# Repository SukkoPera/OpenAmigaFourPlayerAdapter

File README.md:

# OpenAmigaFourPlayerAdapter
OpenAmigaFourPlayerAdapter is an Open Hardware adapter that allows connecting two additional joysticks to Amiga Computers, bringing the total to four.

## Summary
Some Amiga Games support more than the two joysticks you can connect directly to all Amiga models. The two extra joysticks are supposed to be connected to the parallel port through an adapter. OpenAmigaFourPlayerAdapter is an Open Hardware implementation of such an adapter, based on [Tomi Engdahl's Multi-joystick extender circuit](https://www.epanorama.net/documents/joystick/amiga_circuits.html), which claims to be the de-facto standard for this. The same circuit was found on other sources, so this should not be too far away from the actual truth.

The adapter slightly improves that design by also providing 5V power to the joystick ports. Finally, its apparently odd shape allows it not to bump into the nearby power/audio cables that will be connected to your Amiga.

Testing was only carried out with DynaBlaster. [Here is a list](https://aminet.net/package/docs/misc/FourPlayerGames_EN) of more games that *should* hopefully work with it. Actually the list includes the same circuit the adapter is based on, so there are good chances this will be the case. Please report any failures.

## Assembly and Usage
Building the adapter is very easy, just note that you need all male connectors, for both the DB-9 and the DB-25 ports.

The adapter needs no configuration. The only option is whether the 5V power pins of the joystick ports should actually be powered or not. The adapter itself is fully passive and consumes no current. Most old-style joysticks do not need power either, but if you are using one with autofire functionalities or maybe [some "complex" adapter](https://github.com/SukkoPera/OpenPSX2AmigaPadAdapter), it probably will. Now, the problem is that parallel ports are only required to supply a current of 10 mA, which is very little and probably not enough for even the simplest controller that needs power.

Luckily, most (if not all) Amiga models actually go beyond that and are able to provide about 100 mA. I really recommend you to check personally what is inside your Amiga: there should be a  current-limiting resistor connected to pin 14 of the parallel port (It should be labeled E501 on the A500): I found out that this is usually 47 ohm 1/2 W (I checked on an A500 rev 8A, an A600 rev 1.5 and an A1200 rev 1D.4). If this is your case as well, then you will be fine, but **please make sure this applies to your Amiga, or you might blow that resistor**! You have been warned, I take no responsibility!

Once you are sure your Amiga can bear the current, just close the jumper placed near the port(s) of interest.

Finally, please note that you are recommended to **only connect/disconnect the adapter and the joysticks while your Amiga is powered off**, in order to avoid any risk of damage.

## Releases
If you want to get this board produced, you are recommended to get [the latest release](https://github.com/SukkoPera/OpenAmigaFourPlayerAdapter/releases) rather than the current git version, as the latter might be under development and is not guaranteed to be working.

Every release is accompanied by its Bill Of Materials (BOM) file and any relevant notes about it, which you are recommended to read carefully.

**I am not providing ready-to-use gerber files**. If all you want is **to get boards made, I would really appreciate if you did so [in a way that supports the project](#support-the-project)**.

### Enclosure
One 3D-printable enclosure is currently available for this board:

- Kindly contribution by Youen Chéné available in [enclosure](./enclosure) folder. It needs 2 screws for assembly.

## License
The OpenAmigaFourPlayerAdapter documentation, including the design itself, is copyright &copy; SukkoPera 2020.

OpenAmigaFourPlayerAdapter is Open Hardware licensed under the [CERN OHL v. 1.2](http://ohwr.org/cernohl).

You may redistribute and modify this documentation under the terms of the CERN OHL v.1.2. This documentation is distributed *as is* and WITHOUT ANY EXPRESS OR IMPLIED WARRANTIES whatsoever with respect to its functionality, operability or use, including, without limitation, any implied warranties OF MERCHANTABILITY, SATISFACTORY QUALITY, FITNESS FOR A PARTICULAR PURPOSE or infringement. We expressly disclaim any liability whatsoever for any direct, indirect, consequential, incidental or special damages, including, without limitation, lost revenues, lost profits, losses resulting from business interruption or loss of data, regardless of the form of action or legal theory under which the liability may be asserted, even if advised of the possibility or likelihood of such damages.

A copy of the full license is included in file [LICENSE.pdf](LICENSE.pdf), please refer to it for applicable conditions. In order to properly deal with its terms, please see file [LICENSE_HOWTO.pdf](LICENSE_HOWTO.pdf).

The contact points for information about manufactured Products (see section 4.2) are listed in file [PRODUCT.md](PRODUCT.md).

Any modifications made by Licensees (see section 3.4.b) shall be recorded in file [CHANGES.md](CHANGES.md).

The Documentation Location of the original project is https://github.com/SukkoPera/OpenAmigaFourPlayerAdapter/.

## Support the Project
If you want to support the project, you can order the boards from PCBWay through this link:

You get my gratitude and cheap, good quality PCBs, professionally-made. I get some credit that will help with this and [other projects](https://www.pcbway.com/project/member/shareproject/?bmbid=41100). You won't even have to worry about the various PCB options, it's all pre-configured for you!

If you still have to register to that site, [you can use this link](https://www.pcbway.com/setinvite.aspx?inviteid=41100) to get some bonus initial credit (and yield me some more).

You can also buy me a coffee if you want:

## Get Help
If you need help or have any questions or suggestions, you can join `#OpenRetroWorks` on FreeNode through your favorite IRC client or [the webchat](https://webchat.freenode.net/), or [the official Telegram group](https://t.me/joinchat/HUHdWBC9J9JnYIrvTYfZmg).

## Thanks
- Graham P. for sending me the design of a similar adapter he was working on.
- Tomi Engdahl for publishing the circuit.

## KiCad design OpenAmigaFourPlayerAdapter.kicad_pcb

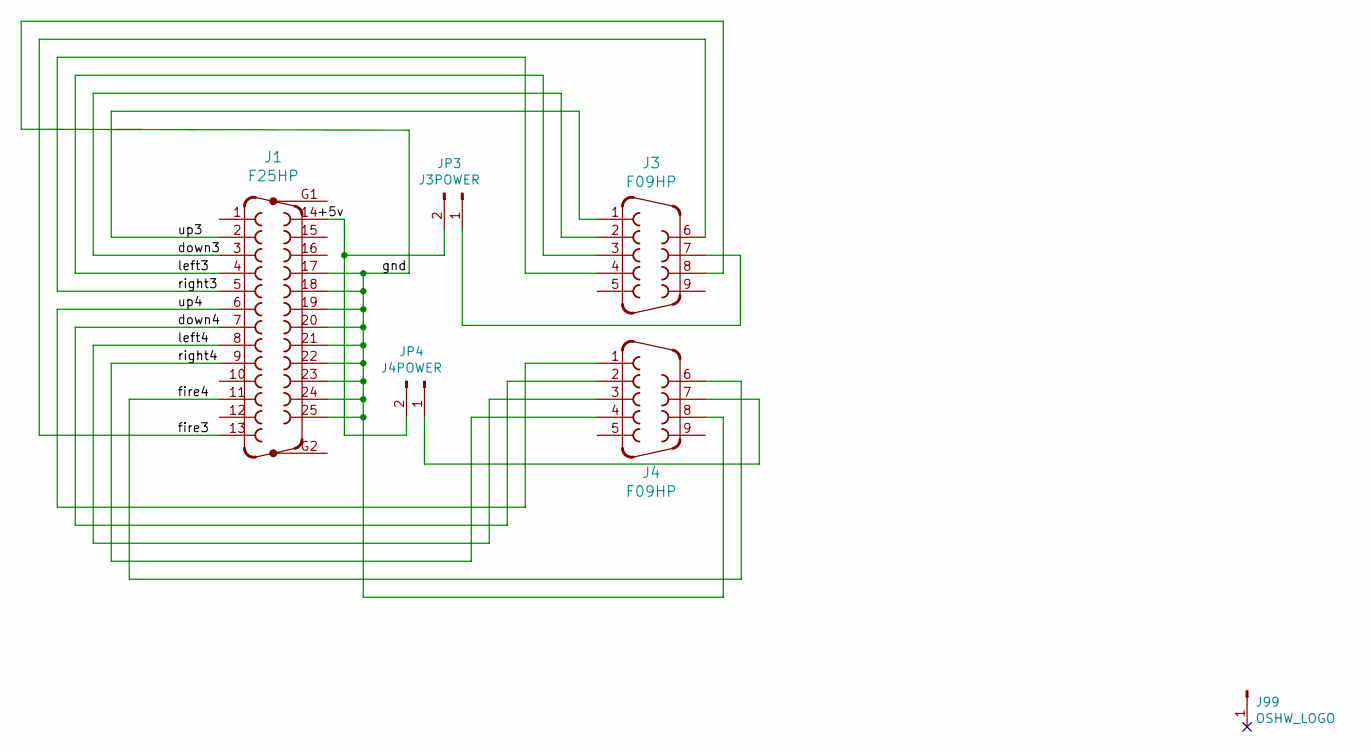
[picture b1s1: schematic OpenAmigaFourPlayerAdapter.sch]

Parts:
J1: F25HP; DSUB-25_Male_EdgeMount_P2.77mm
J3, J4: F09HP; DSUB-9_Male_EdgeMount_P2.77mm
J99: OSHW_LOGO; OSHW-Logo_5.7x6mm_Copper
JP3: J3POWER; PinHeader_1x02_P2.54mm_Vertical
JP4: J4POWER; PinHeader_1x02_P2.54mm_Vertical

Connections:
/+5v: J1.14, JP3.2, JP4.2
/down3: J1.3, J3.2
/down4: J1.7, J4.2
/fire3: J1.13, J3.6
/fire4: J1.11, J4.6
/gnd: J1.17, J1.18, J1.19, J1.20, J1.21, J1.22, J1.23, J1.24, J1.25, J3.8, J4.8
/left3: J1.4, J3.3
/left4: J1.8, J4.3
/right3: J1.5, J3.4
/right4: J1.9, J4.4
/up3: J1.2, J3.1
/up4: J1.6, J4.1
unnamed: J3.7, JP3.1
unnamed: J4.7, JP4.1

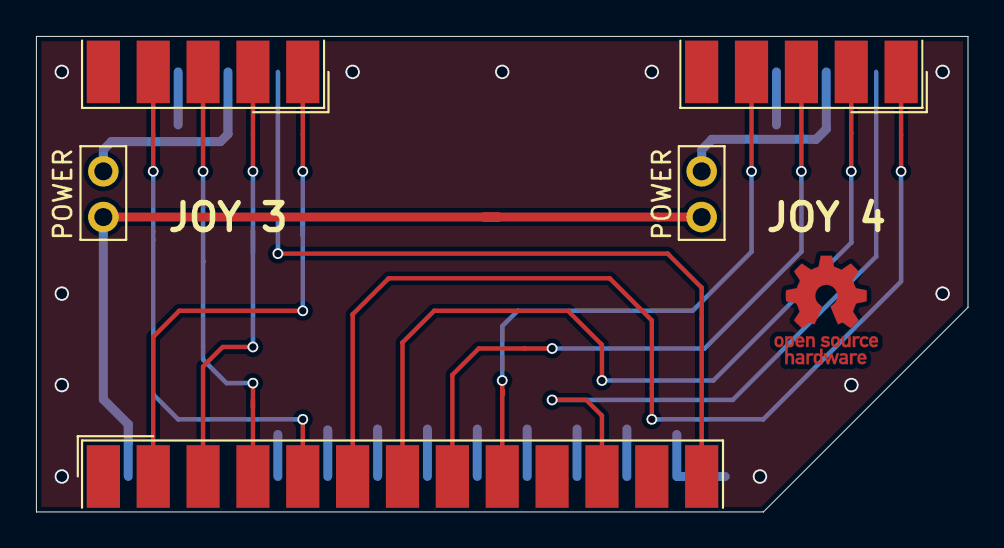
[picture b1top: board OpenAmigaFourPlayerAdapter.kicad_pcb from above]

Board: 2 copper layers, 51.8 x 26.4 mm, 6 parts (0 on the bottom side), 14 nets.

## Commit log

2020-01-02 4 Player Adapter.* -> OpenAmigaFourPlayerAdapter.*
2020-02-11 Add 3D model for DB-9 connector
2020-02-11 Fix minor issue with copper pour
2020-02-11 Make shape symmetrical (but not yet suitable for A600/1200)
2020-02-17 Change shape so that we don't bump in audio connectors on A600/A1200
2020-02-18 Fix board outline
2020-02-18 Make board slightly shorter
2020-02-18 Add renders
2020-02-18 Add license
2020-02-18 Add README.md
2020-02-19 Fix credits
2020-02-22 Improve ground stitching
2020-03-19 Ready for V2
2020-05-24 Add fp-info-cache to .gitignore
2020-05-24 Fix boards link
2020-05-24 Add social image
2023-05-15 feat: add 3D printed enclosure
2023-11-04 feat: new enclosure for m3 screws

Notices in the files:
OpenAmigaFourPlayerAdapter.kicad_pcb:
Licensed under CERN OHL v.1.2
